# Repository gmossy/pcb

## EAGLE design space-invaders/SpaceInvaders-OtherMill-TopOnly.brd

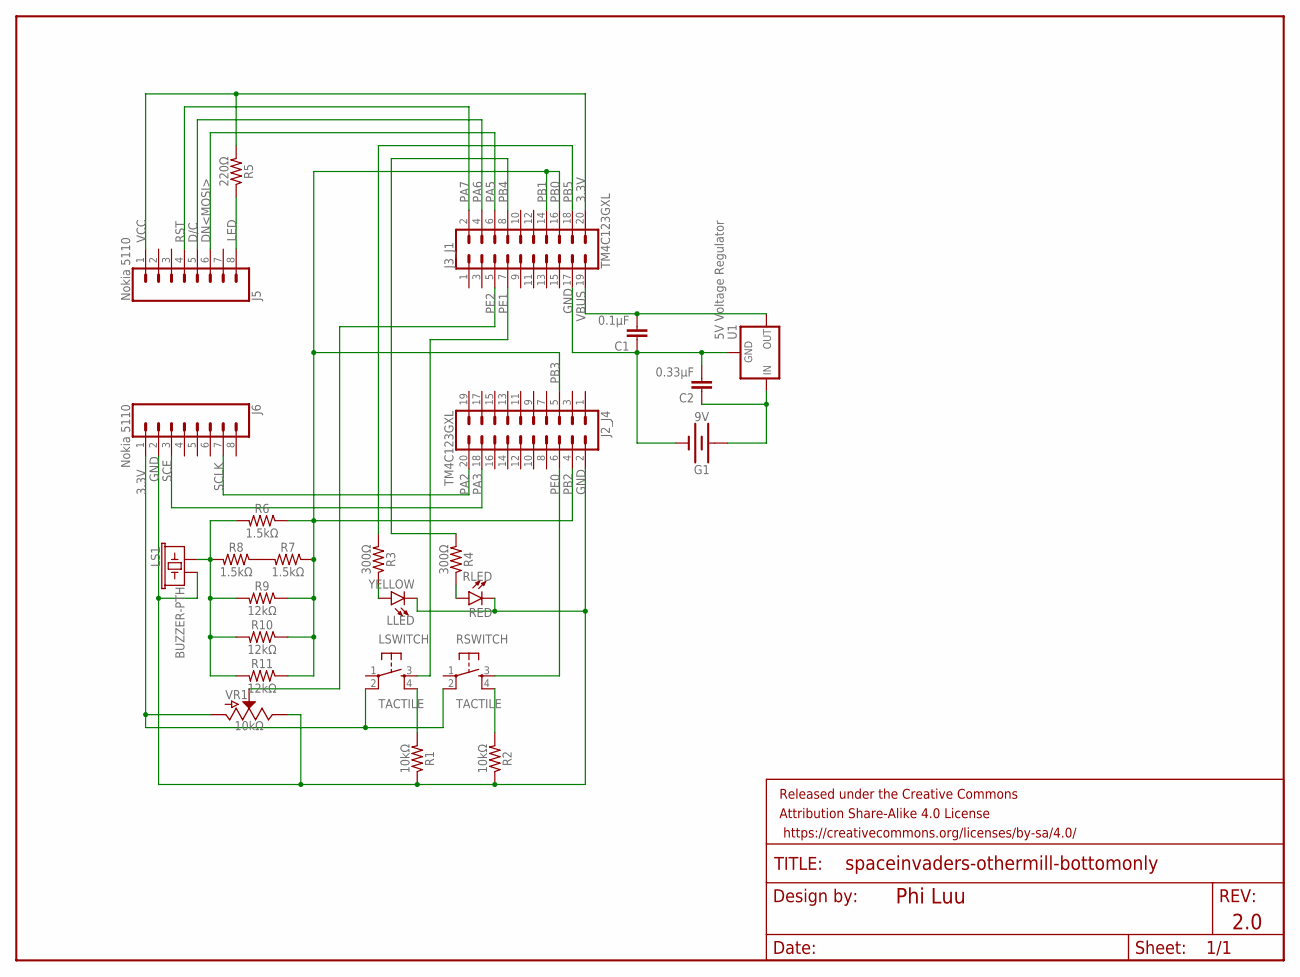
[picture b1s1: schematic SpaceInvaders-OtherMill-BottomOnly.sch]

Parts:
C1: 0.1μF; CAP-PTH-SMALL-KIT
C2: 0.33μF; CAP-PTH-SMALL-KIT
FRAME1: FRAME-LETTER; CREATIVE_COMMONS
G1: 9V; BATTCON_9V
J2_J4, J3_J1: TM4C123GXL; 2X10
J5, J6: Nokia 5110; 1X08
LLED: YELLOW; LED_5MM
LS1: BUZZER-PTH; BUZZER-12MM
LSWITCH: TACTILE; TACTILE-PTH
R1, R2: 10kΩ; AXIAL-0.3
R3, R4: 300Ω; AXIAL-0.3
R5: 220Ω; AXIAL-0.3
R6, R7, R8: 1.5kΩ; AXIAL-0.3
R9, R10, R11: 12kΩ; AXIAL-0.3
RLED: RED; LED_5MM
RSWITCH: TACTILE; TACTILE-PTH
U1: 5V Voltage Regulator; TO-220-ALT
VR1: 10kΩ; SLIDER-MEDIUM

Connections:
3.3V: J3_J1.20, J5.1, J6.1, LSWITCH.2, R5.P$2 (2), RSWITCH.2, VR1.BOTTOM (A)
9V: C2.1, G1.+, U1.IN
GND: C1.1, C2.2, G1.-, J2_J4.2, J3_J1.17, J6.2, LLED.K (C), LS1.- (2), R1.P$1 (1), R2.P$1 (1), RLED.K (C), U1.GND, VR1.TOP (E)
LED: J5.8, R5.P$1 (1)
unnamed: R7.P$2 (2), R8.P$1 (1)
unnamed: LSWITCH.4, R1.P$2 (2)
unnamed: R2.P$2 (2), RSWITCH.4
unnamed: R4.P$1 (1), RLED.A
unnamed: LLED.A, R3.P$1 (1)
unnamed: LS1.+ (1), R6.P$2 (2), R8.P$2 (2), R9.P$2 (2), R10.P$2 (2), R11.P$2 (2)
PA2: J2_J4.20, J6.7
PA3: J2_J4.18, J6.3
PA5: J3_J1.6, J5.6
PA6: J3_J1.4, J5.5
PA7: J3_J1.2, J5.4
PB2: J2_J4.4, J2_J4.5, J3_J1.14, J3_J1.16, R6.P$1 (1), R7.P$1 (1), R9.P$1 (1), R10.P$1 (1), R11.P$1 (1)
PB4: J3_J1.8, R4.P$2 (2)
PB5: J3_J1.18, R3.P$2 (2)
PE0: J2_J4.6, RSWITCH.3
PE1: J3_J1.7, LSWITCH.3
PE2: J3_J1.5, VR1.WIPER (S)
VBUS: C1.2, J3_J1.19, U1.OUT

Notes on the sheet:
Phi Luu
2.0
PB0
PB1
PB3
VCC
RST
D/C
DN<MOSI>
SCE
SCLK

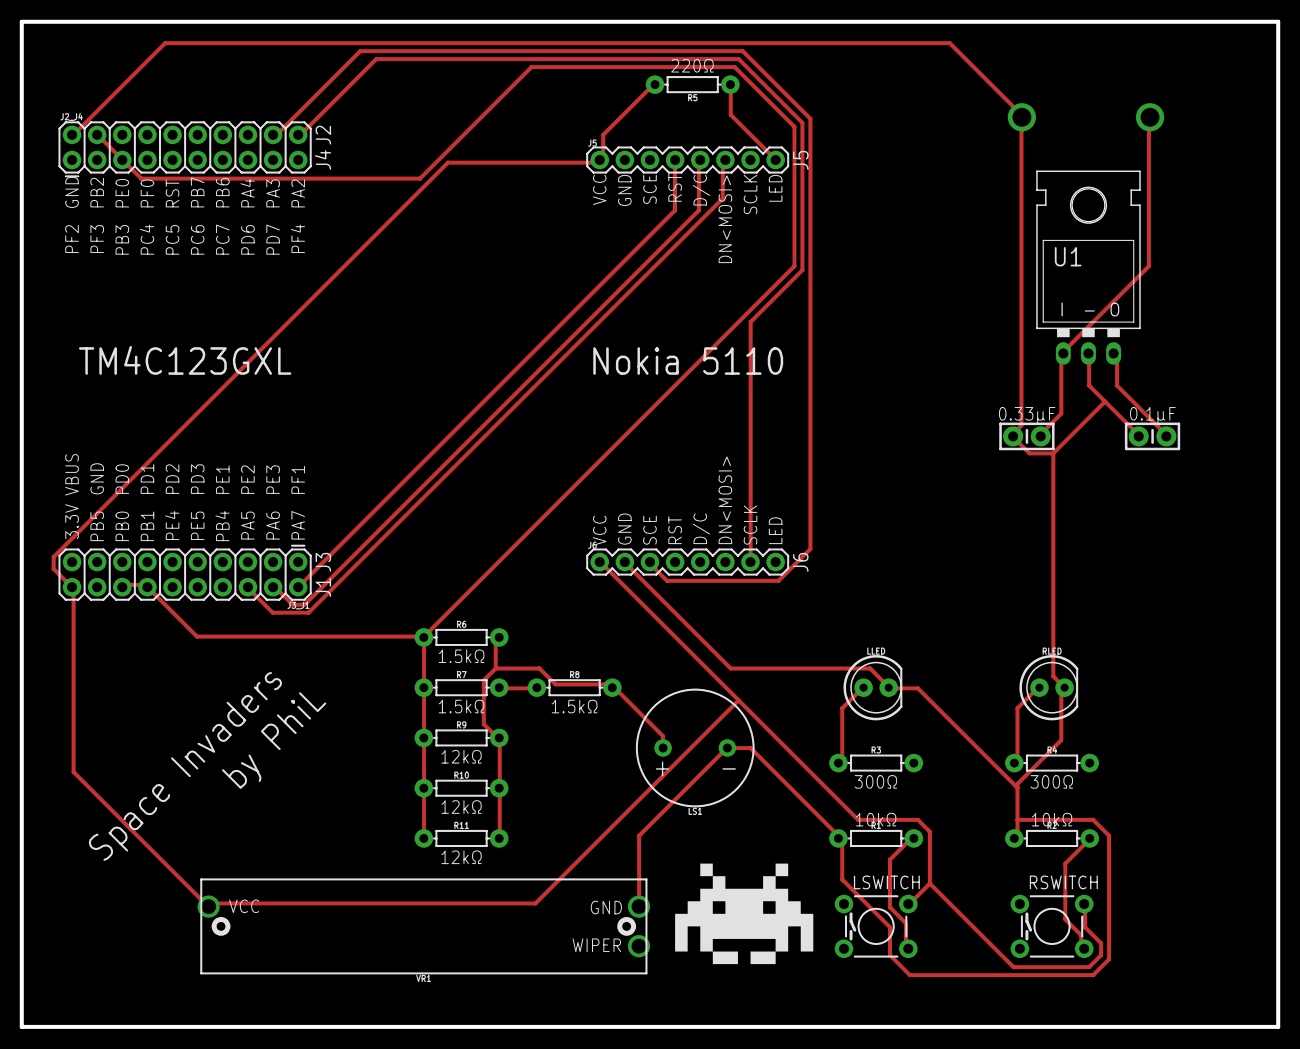
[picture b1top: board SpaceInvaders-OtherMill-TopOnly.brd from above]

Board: 2 copper layers, 127.0 x 101.6 mm, 26 parts (1 on the bottom side), 22 nets.

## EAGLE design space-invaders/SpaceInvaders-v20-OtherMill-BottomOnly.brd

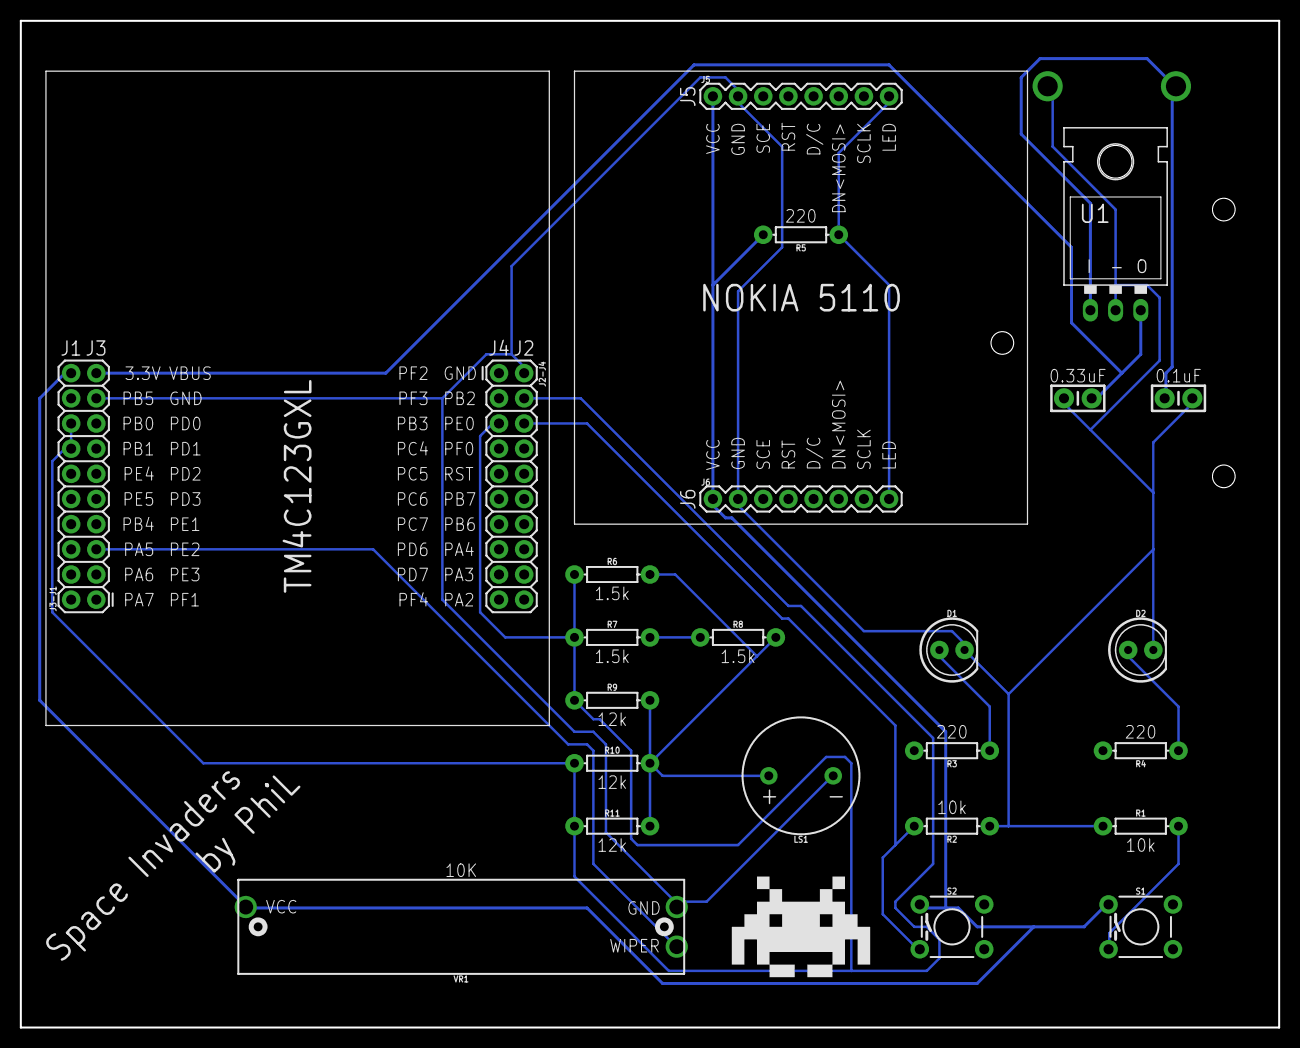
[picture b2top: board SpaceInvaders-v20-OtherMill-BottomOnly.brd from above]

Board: 2 copper layers, 127.0 x 101.6 mm, 26 parts (1 on the bottom side), 20 nets.

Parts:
C1: 0.1uF; CAP-PTH-SMALL-KIT
C2: 0.33uF; CAP-PTH-SMALL-KIT
D1: RED; LED_5MM
D2: YELLOW; LED_5MM
FRAME1: FRAME-LETTER; CREATIVE_COMMONS
J2-J4, J3-J1: TM4C123GXL; 2X10
J5, J6: Nokia_5110; 1X08
J7: 9V; BC9VPC
LS1: BUZZER; BUZZER-12MM
R1, R2: 10k; AXIAL-0.3
R3, R4, R5: 220; AXIAL-0.3
R6, R7, R8: 1.5k; AXIAL-0.3
R9, R10, R11: 12k; AXIAL-0.3
S1: SPECIAL; TACTILE_SWITCH_PTH_6.0MM
S2: REGULAR; TACTILE_SWITCH_PTH_6.0MM
U1: LM7805CT; TO-220-ALT
VR1: 10k; SLIDER-MEDIUM

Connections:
3.3V: J3-J1.20, J5.1, J6.1, R5.P$2, S1.1, S2.1, VR1.BOTTOM
9V: C2.1, J7.V+, U1.IN
DAC_OUT: LS1.+, R6.P$2, R8.P$2, R9.P$2, R10.P$2, R11.P$2
GND: C1.1, C2.2, D1.K, D2.K, J2-J4.2, J3-J1.17, J5.2, J6.2, J7.V-, LS1.-, R1.P$1, R2.P$1, U1.GND, VR1.TOP
LED: J5.8, J6.8, R5.P$1
LLED: D1.A, R3.P$1
unnamed: R7.P$2, R8.P$1
PA2: J2-J4.20, J6.7
PA3: J2-J4.18, J6.3
PA5: J3-J1.6, J5.6
PA6: J3-J1.4, J5.5
PA7: J3-J1.2, J5.4
PB2: J2-J4.4, J2-J4.5, J3-J1.14, J3-J1.16, R6.P$1, R7.P$1, R9.P$1, R10.P$1, R11.P$1
PB4: J3-J1.8, R4.P$2
PB5: J3-J1.18, R3.P$2
PE0: J2-J4.6, R2.P$2, S2.3
PE1: J3-J1.7, R1.P$2, S1.3
PE2: J3-J1.5, VR1.WIPER
RLED: D2.A, R4.P$1
VBUS: C1.2, J3-J1.19, U1.OUT

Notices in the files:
parts and their libraries:
SparkFun-Connectors: Licensing: Creative Commons ShareAlike 4.0 International - https://creativecommons.org/licenses/by-sa/4.0
SparkFun-Aesthetics: Released under the Creative Commons Attribution Share-Alike 4.0 License
SparkFun-Aesthetics: https://creativecommons.org/licenses/by-sa/4.0
